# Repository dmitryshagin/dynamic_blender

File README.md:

# Dynamic trimix blender 
**This project includes both hardware description & all needed software and firmware.**

Blender is built to mix EAN and Trimix mixtures dynamically, with no more than 40% of oxygen.

Main electronic components:
* MCU: Atmega64. 16 or 32kB versions could be used with no/minimum code changes (untested).
* ADC: AD7793. Used to get accurate O2 readings.
* Any oxygen sensors with 7-25mV @ 21% O2 output could be used without any changes.

Software needed to work with schematic and board:
* [Eagle](http://www.cadsoftusa.com/download-eagle/) for schematic and board. Free version is enough.
* [FreeRouting](http://www.freerouting.net/) - was used for initial routing. Optional.
* [Gerbv](http://gerbv.sourceforge.net/) to preview gerbers. Optional - just to control them before factory processing.

I've ordered PCB's at [SeeedStudio](http://www.seeedstudio.com/service/index.php?r=pcb), but feel free to use any PCB factory with equivalent capabilities. Board size is 44x122mm.

Developed by [DiveTeam](http://diveteam.com.ua) :rowboat:

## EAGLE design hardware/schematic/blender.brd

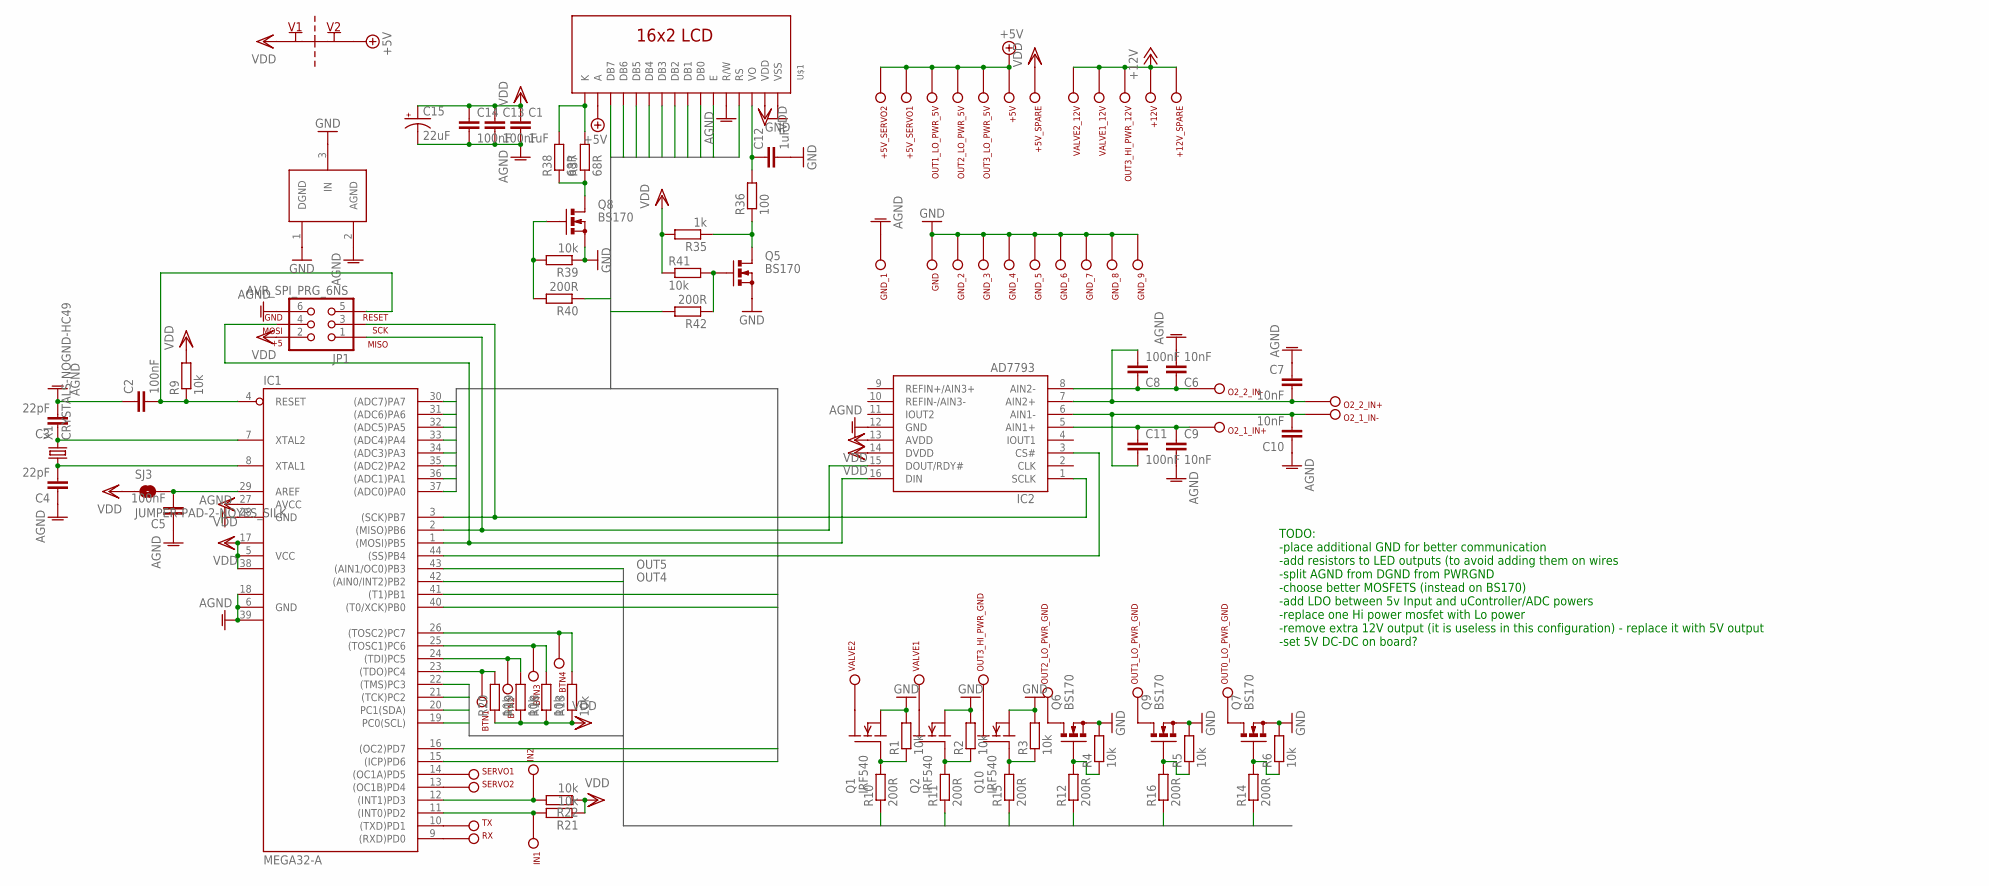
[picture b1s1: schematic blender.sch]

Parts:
+5V, +5V_SERVO1, +5V_SERVO2, +5V_SPARE, +12V, +12V_SPARE: PIN
BTN1, BTN2, BTN3, BTN4: PIN
C1, C12: 1uF; C0603
C2, C5, C8, C11, C13, C14: 100nF; C0603
C3, C4: 22pF; C0603
C6, C7, C9, C10: 10nF; C0603
C15: 22uF; EIA7343
GND: PIN
GND_1, GND_2, GND_3, GND_4, GND_5, GND_6, GND_7, GND_8, GND_9: PIN
IC1: MEGA32-A; TQFP44
IC2: AD7793; TSSOP16
IN1, IN2: PIN
JP1: AVR_SPI_PRG_6NS; 2X3-NS
O2_1_IN+, O2_1_IN-, O2_2_IN+, O2_2_IN-: PIN
OUT0_LO_PWR_GND, OUT1_LO_PWR_5V, OUT1_LO_PWR_GND, OUT2_LO_PWR_5V, OUT2_LO_PWR_GND, OUT3_HI_PWR_12V, OUT3_HI_PWR_GND, OUT3_LO_PWR_5V: PIN
Q1, Q2, Q10: IRF540; TO220
Q5, Q6, Q7, Q8, Q9: BS170; SOT54E
R1, R2, R3, R4, R5, R6, R9, R13, R18, R19, R20, R21, R22, R39, R41: 10k; R0603
R10, R11, R12, R14, R15, R16, R40, R42: 200R; R0603
R35: 1k; R0603
R36: 100; R0603
R37, R38: 68R; R1206
RX: PIN
SERVO1, SERVO2: PIN
SJ3: JUMPER-PAD-2-NOYES_SILK; PAD-JUMPER-2-NO_YES_SILK
TX: PIN
U$1: 1602L
U$2: SUPPLY_CONNECT; 2PT_GND_TIE
U$3: GND_CONNECT
VALVE1, VALVE1_12V, VALVE2, VALVE2_12V: PIN
X1: CRYSTALS-NOGND-HC49; HC49

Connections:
+5V: +5V.P$1, +5V_SERVO1.P$1, +5V_SERVO2.P$1, OUT1_LO_PWR_5V.P$1, OUT2_LO_PWR_5V.P$1, OUT3_LO_PWR_5V.P$1, U$1.P$15 (A), U$2.P$2
+12V: +12V.P$1, +12V_SPARE.P$1, OUT3_HI_PWR_12V.P$1, VALVE1_12V.P$1, VALVE2_12V.P$1
AGND: C1.2, C2.1, C3.2, C4.1, C5.1, C6.2, C7.1, C9.2, C10.1, C13.2, C14.2, C15.C (-), GND_1.P$1, IC1.6 (GND), IC1.18 (GND1), IC1.28 (GND), IC1.39 (GND2), IC2.12 (GND), JP1.6, U$1.P$5 (R/W), U$3.2 (AGND)
BACKLIGHT: IC1.16 ((OC2)PD7), R40.1
CONTRAST: IC1.15 ((ICP)PD6), R42.2
DB0: IC1.37 ((ADC0)PA0), U$1.P$7 (DB0)
DB1: IC1.36 ((ADC1)PA1), U$1.P$8 (DB1)
DB2: IC1.35 ((ADC2)PA2), U$1.P$9 (DB2)
DB3: IC1.34 ((ADC3)PA3), U$1.P$10 (DB3)
DB4: IC1.33 ((ADC4)PA4), U$1.P$11 (DB4)
DB5: IC1.32 ((ADC5)PA5), U$1.P$12 (DB5)
DB6: IC1.31 ((ADC6)PA6), U$1.P$13 (DB6)
DB7: IC1.30 ((ADC7)PA7), U$1.P$14 (DB7)
E: IC1.40 ((T0/XCK)PB0), U$1.P$6 (E)
GND: C12.2, GND.P$1, GND_2.P$1, GND_3.P$1, GND_4.P$1, GND_5.P$1, GND_6.P$1, GND_7.P$1, GND_8.P$1, GND_9.P$1, Q1.3 (S), Q2.3 (S), Q5.S, Q6.S, Q7.S, Q8.S, Q9.S, Q10.3 (S), R1.2, R2.2, R3.2, R4.2, R5.2, R6.2, R39.1, U$1.P$1 (VSS), U$3.1 (DGND), U$3.3 (IN)
unnamed: Q5.D, R35.1, R36.1
unnamed: C12.1, R36.2, U$1.P$3 (VO)
unnamed: Q8.D, R37.1, R38.1
unnamed: R37.2, R38.2, U$1.P$16 (K)
unnamed: Q8.G, R39.2, R40.2
unnamed: IC1.1 ((MOSI)PB5), IC2.16 (DIN), JP1.4
unnamed: IC1.2 ((MISO)PB6), IC2.15 (DOUT/RDY#), JP1.1
unnamed: IC1.3 ((SCK)PB7), IC2.1 (SCLK), JP1.3
unnamed: IC1.44 ((SS)PB4), IC2.3 (CS#)
unnamed: C2.2, IC1.4 (RESET), JP1.5, R9.1
unnamed: Q5.G, R41.2, R42.1
unnamed: C3.1, IC1.7 (XTAL2), X1.2
unnamed: C4.2, IC1.8 (XTAL1), X1.1
unnamed: Q1.1 (G), R1.1, R10.2
unnamed: Q2.1 (G), R2.1, R11.2
unnamed: Q10.1 (G), R3.1, R15.2
unnamed: BTN3.P$1, IC1.25 ((TOSC1)PC6), R18.2
unnamed: Q7.G, R6.1, R14.2
unnamed: Q6.G, R4.1, R12.2
unnamed: Q9.G, R5.1, R16.2
unnamed: C5.2, IC1.29 (AREF), SJ3.2
unnamed: IC1.12 ((INT1)PD3), IN2.P$1, R22.2
unnamed: IC1.11 ((INT0)PD2), IN1.P$1, R21.2
unnamed: BTN4.P$1, IC1.26 ((TOSC2)PC7), R13.2
unnamed: BTN2.P$1, IC1.24 ((TDI)PC5), R19.2
unnamed: BTN1.P$1, IC1.23 ((TDO)PC4), R20.2
unnamed: IC1.9 ((RXD)PD0), RX.P$1
unnamed: IC1.10 ((TXD)PD1), TX.P$1
unnamed: IC1.14 ((OC1A)PD5), SERVO1.P$1
unnamed: IC1.13 ((OC1B)PD4), SERVO2.P$1
unnamed: Q2.2 (D), VALVE1.P$1
unnamed: Q1.2 (D), VALVE2.P$1
unnamed: OUT3_HI_PWR_GND.P$1, Q10.2 (D)
unnamed: OUT0_LO_PWR_GND.P$1, Q7.D
unnamed: OUT1_LO_PWR_GND.P$1, Q9.D
unnamed: OUT2_LO_PWR_GND.P$1, Q6.D
unnamed: C10.2, C11.2, IC2.6 (AIN1-), O2_1_IN-.P$1
unnamed: C7.2, C8.2, IC2.7 (AIN2+), O2_2_IN+.P$1
unnamed: C6.1, C8.1, IC2.8 (AIN2-), O2_2_IN-.P$1
unnamed: C9.1, C11.1, IC2.5 (AIN1+), O2_1_IN+.P$1
OUT0: IC1.19 (PC0(SCL)), R14.1
OUT1: IC1.20 (PC1(SDA)), R16.1
OUT2: IC1.21 ((TCK)PC2), R12.1
OUT3: IC1.22 ((TMS)PC3), R15.1
OUT4: IC1.42 ((AIN0/INT2)PB2), R11.1
OUT5: IC1.43 ((AIN1/OC0)PB3), R10.1
RS: IC1.41 ((T1)PB1), U$1.P$4 (RS)
VDD: +5V_SPARE.P$1, C1.1, C13.1, C14.1, C15.A (+), IC1.5 (VCC), IC1.17 (VCC1), IC1.27 (AVCC), IC1.38 (VCC2), IC2.13 (AVDD), IC2.14 (DVDD), JP1.2, R9.2, R13.1, R18.1, R19.1, R20.1, R21.1, R22.1, R35.2, R41.1, SJ3.1, U$1.P$2 (VDD), U$2.P$1

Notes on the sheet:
TODO: -place additional GND for better communication -add resistors to LED outputs (to avoid adding them on wires -split AGND from DGND from PWRGND -choose better MOSFETS (instead on BS170) -add LDO between 5v Input and uController/ADC powers -replace one Hi power mosfet with Lo power -remove extra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

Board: 2 copper layers, 100 parts (44 on the bottom side), 63 nets, no tracks yet.

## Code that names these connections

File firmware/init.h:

#ifndef __INIT_H__
#define __INIT_H__

#include <avr/io.h>
#include "pid.h"

#define O2_COEFF 209460000UL

#define SERVO1 0
#define SERVO2 1

#define VALVE1_ON 			(PORTB |=  (1<<PB2))
#define VALVE1_OFF 			(PORTB &= ~(1<<PB2))
#define VALVE2_ON 			(PORTB |=  (1<<PB3))
#define VALVE2_OFF 			(PORTB &= ~(1<<PB3))
#define LED_VAVLE1_ON 		(PORTC |=  (1<<PC2))
#define LED_VAVLE1_OFF 		(PORTC &= ~(1<<PC2))
#define LED_VAVLE2_ON	 	(PORTC |=  (1<<PC0))
#define LED_VAVLE2_OFF 		(PORTC &= ~(1<<PC0))
#define LED_ALERT_ON 		(PORTC |=  (1<<PC1))
#define LED_ALERT_OFF 		(PORTC &= ~(1<<PC1))
#define BUZZER_ON 			(PORTC |=  (1<<PC3))
#define BUZZER_OFF 			(PORTC &= ~(1<<PC3))
#define COMPRESSOR_IS_ON  	(!(PIND  & (1<<PD2))) 
#define FLOW_IS_ON  		(!(PIND  & (1<<PD3)))

#define BUTTON_PLUS_PRESSED 	(!(PINC & (1 << PC4)))
#define BUTTON_MINUS_PRESSED 	(!(PINC & (1 << PC5)))
#define BUTTON_ENTER_PRESSED 	(!(PINC & (1 << PC6)))
#define BUTTON_EXIT_PRESSED 	(!(PINC & (1 << PC7)))

#define ANY_BUTTON_PRESSED (BUTTON_PLUS_PRESSED||BUTTON_MINUS_PRESSED||BUTTON_ENTER_PRESSED||BUTTON_EXIT_PRESSED)
#define ALL_BUTTONS_RELEASED (!ANY_BUTTON_PRESSED)


#define MODE_EMERGENCY 1

#define MODE_CALIBRATE 10
#define MODE_MIXING 11

#define MODE_SET_O2 20
#define MODE_SET_HE 21

#define MODE_SET_BRIGHTNESS 50
#define MODE_SET_CONTRAST 51
#define MODE_SET_EMERGENCY_LEVEL 52
#define MODE_SET_SENSOR_USAGE 53
#define MODE_SET_VALVE1 60
#define MODE_SET_VALVE2 61
#define MODE_RUN_TEST 70
#define MODE_START_CALIBRATE 71
#define MODE_SET_PID 81
#define MODE_SET_SERVO1_MIN 91
#define MODE_SET_SERVO1_MAX 92
#define MODE_SET_SERVO2_MIN 93
#define MODE_SET_SERVO2_MAX 94
#define MODE_SET_TIMER1 95

typedef struct TARGET_MIX{
  uint16_t oxygen;
  uint32_t helium;
  uint16_t real_oxygen;
  uint32_t real_helium;
} targetMix_t;

typedef struct SENSORS_TARGET_MIX{
  uint32_t s1_target; //is calculated for desired mix. For Nitrox equals target_oxygen
  uint32_t s2_target;
  uint8_t valve1_target;
  uint8_t valve2_target;
} sensorsTargetMix_t;


typedef struct SENSORS_DATA{	
	uint32_t s1_uV;
	uint32_t s2_uV; 
	uint32_t s1_O2;
	uint32_t s2_O2;
	int64_t	 s1_coeff;
	int64_t  s2_coeff;
} sensors_t;


typedef struct PID_FACTORS{	
	int16_t s1_p_factor;
	int16_t s1_i_factor;
	int16_t s1_d_factor;
	int16_t	s1_max_output;
	int16_t s2_p_factor;
	int16_t s2_i_factor;
	int16_t s2_d_factor;
	int16_t	s2_max_output;
} pid_factors_t;


typedef struct SYSTEM_CONFIG{
	uint16_t min_servo_1; 
	uint16_t min_servo_2;
	uint16_t max_servo_1;
	uint16_t max_servo_2;
	uint16_t servo_timer_period_icr_top;
	uint8_t brightness;
	uint8_t contrast;
	uint16_t oxygen_emergency_limit;
	uint8_t use_only_first_sensor;
} systemConfig_t;

typedef struct BUTTONS_STATUS{
	uint8_t buttonPlus;
	uint8_t buttonMinus;
} buttonsStatus_t;

extern struct SYSTEM_CONFIG system_config;
extern struct TARGET_MIX target;
extern struct SENSORS_TARGET_MIX sensors_target;
extern struct SENSORS_DATA s_data;
extern struct BUTTONS_STATUS buttons;
extern struct PID_FACTORS pid_factors;
extern uint32_t log_windows[2][10];
extern uint8_t  log_position[2];
extern struct PID_DATA pidData1; 
extern struct PID_DATA pidData2;



int8_t parseInt(char * input, uint8_t max_count,int *result,int min_allowed,int max_allowed);

uint8_t is_log_ok();

void init_outputs();

void init();

void set_servo(uint8_t servo, int16_t value);

void set_brightness(uint8_t value);

void set_contrast(uint8_t value);

uint8_t check_emergency();

void uart_init( void );

void test_outputs();

void save_eeprom_data();

void save_target_to_eeprom();

void save_pid_data_to_eeprom();

uint16_t get_uptime_seconds();

void reset_need_input();

uint8_t need_input();

uint8_t is_calibrated_values_ok();

uint8_t need_blink();

uint8_t need_buzz();

void reset_blink();

void reset_buzz();

void set_alert(uint8_t blink, uint8_t buzz);

void process_alert();

void check_alert();

uint32_t get_max_deviation();


#endif	// _INIT_H_

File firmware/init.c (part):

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	DDRB |= (1 << 3) | (1 << 2); 
	DDRC |= (1 << 0) | (1 << 1) | (1 << 2) | (1 << 3);	
	DDRD |= (1 << 6) | (1 << 7); //Contrast & Brightness
    DDRD &= ~(1 << PD2);
    DDRD &= ~(1 << PD3);
    PORTD |= (1<<PD2);
    PORTD |= (1<<PD3);

    DDRC &= ~(1 << PC4);
    DDRC &= ~(1 << PC5);
    DDRC &= ~(1 << PC6);
    DDRC &= ~(1 << PC7);
    PORTC |= (1<<PC4);
    PORTC |= (1<<PC5);
    PORTC |= (1<<PC6);
    PORTC |= (1<<PC7);


	TCCR2A |= (1 << WGM20 | 1 << WGM21) | (1 << COM2A1) | (1 << COM2B1);
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    ICR1=system_config.servo_timer_period_icr_top;  //fPWM=50Hz (Period = 20ms Standard).
    // Timer period - 3.4722uS

    DDRD|=(1<<PD4)|(1<<PD5);   //PWM Pins as Out

    OCR1A=system_config.min_servo_1;   //0 degree (0.388ms)
    OCR1B=system_config.min_servo_2;
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
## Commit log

2015-05-15 Initial commit - added first version of hardware
2015-05-30 initial firmware setup (just checked peripherial devices)
2015-06-04 some refactoring
2015-06-05 Added PID, UART, EEPROM libraries. Some refactoring
2015-06-30 buttons - conect
2015-06-30 some tweaks for schematic (board destroyed), added TODOs for sch (inside sch)
2015-07-02 IO basic check
2015-07-06 added bootloader
2015-07-09 some small work done
2015-07-24 started to work on menu
2015-07-24 added some items to menu
2015-07-24 added progressbar for brightness and contrast
2015-07-25 menu, 1st iteration complete (no floating menus left at the moment. will add extra info on mixing screen and refactor it later
2015-07-27 menu is ready for refactoring
2015-07-27 slight refactoring
2015-07-27 some more refactoring
2015-07-28 pre-alpha release - ready to setup PID
2015-07-29 debug PID - just for desktop
2015-07-29 extended valved from 0-100 to 0-255
2015-07-30 some cosmetic fixes
2015-07-30 added alert
2015-07-30 some code cleanup, helium check added
2015-07-30 polishing fixes
2015-07-30 bugfix - changed o2 value after calibration
2015-07-31 added some more checks
2015-08-06 PID started to work
2015-08-07 PID some tuning
2015-08-09 some menu refactoring
2015-08-09 moved PID to EEPROM
2015-08-09 added PID setup to menu
2015-08-09 first reply to uart
2015-08-10 added timer config to lcd menu (untested)
2015-08-10 added UART comunication. untested
2015-08-10 moved uart output to progmem. we are now fitting to mega32 again. mega16 is pretty much unreachable without serious refactoring
2015-08-11 added uart
2015-08-11 tested UART
2015-08-12 changed servo max setup
2015-08-13 added pid limit to config
2015-08-20 rebuild
2015-08-21 set calibration to first screen, added max value setup for PID
2015-08-21 lowered max allowed deviation, and oxy limit
2015-09-15 Added minimum helium for hypoxy mixes
2015-09-15 chenged initial EEPROM values
2015-09-22 Added display of resulting mix with decimal points. Doubled PID input resolution
2015-09-22 Added some rounding for better accuracy (PID setup with maximum 0.025% error)
2015-11-14 pressostat fix
2018-01-13 Added ability to work just with 1 sensor, extended UART output

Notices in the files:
parts and their libraries:
SparkFun-Connectors: Licensing: Creative Commons ShareAlike 4.0 International - https://creativecommons.org/licenses/by-sa/4.0
